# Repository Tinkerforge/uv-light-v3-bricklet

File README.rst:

UV Light Bricklet 3.0
=====================

This repository contains the firmware source code and the hardware design
files. The documentation generator configs can be found at
https://github.com/Tinkerforge/generators

Repository Content
------------------

software/:
 * examples/: Examples for all supported languages
 * build/: Compiled files
 * src/: Source code of firmware
 * Makefile: Makefile to build project

hardware/:
 * Contains KiCad project files and additionally schematics as PDF

datasheets/:
 * Contains datasheets for sensors and complex ICs that are used

Hardware
--------

The hardware is designed with the open source EDA Suite KiCad
(http://www.kicad.org). Before you are able to open the files,
you have to install the Tinkerforge kicad-libraries
(https://github.com/Tinkerforge/kicad-libraries). You can either clone
them directly in hardware/ or clone them in a separate folder and
symlink them into hardware/
(ln -s kicad_path/kicad-libraries project_path/hardware). After that you
can open the .pro file in hardware/ with KiCad and from there view and
modify the schematics and the PCB layout.

Software
--------

If you want to do your own Brick/Bricklet firmware development we highly
recommend that you use our build environment setup script and read the
tutorial (https://www.tinkerforge.com/en/doc/Tutorials/Tutorial_Build_Environment/Tutorial.html).

To compile the C code we recommend you to install the newest GNU Arm Embedded
Toolchain (https://launchpad.net/gcc-arm-embedded/+download).
You also need to install bricklib2 (https://github.com/Tinkerforge/bricklib2).

You can either clone it directly in software/src/ or clone it in a
separate folder and symlink it into software/src/
(ln -s bricklib_path/bricklib2 project_path/software/src/). Finally make sure to
have CMake installed (http://www.cmake.org/cmake/resources/software.html).

After that you can build the firmware by invoking make in software/.
The firmware (.zbin) can then be found in software/build/ and uploaded
with brickv (click button "Flashing" on start screen).

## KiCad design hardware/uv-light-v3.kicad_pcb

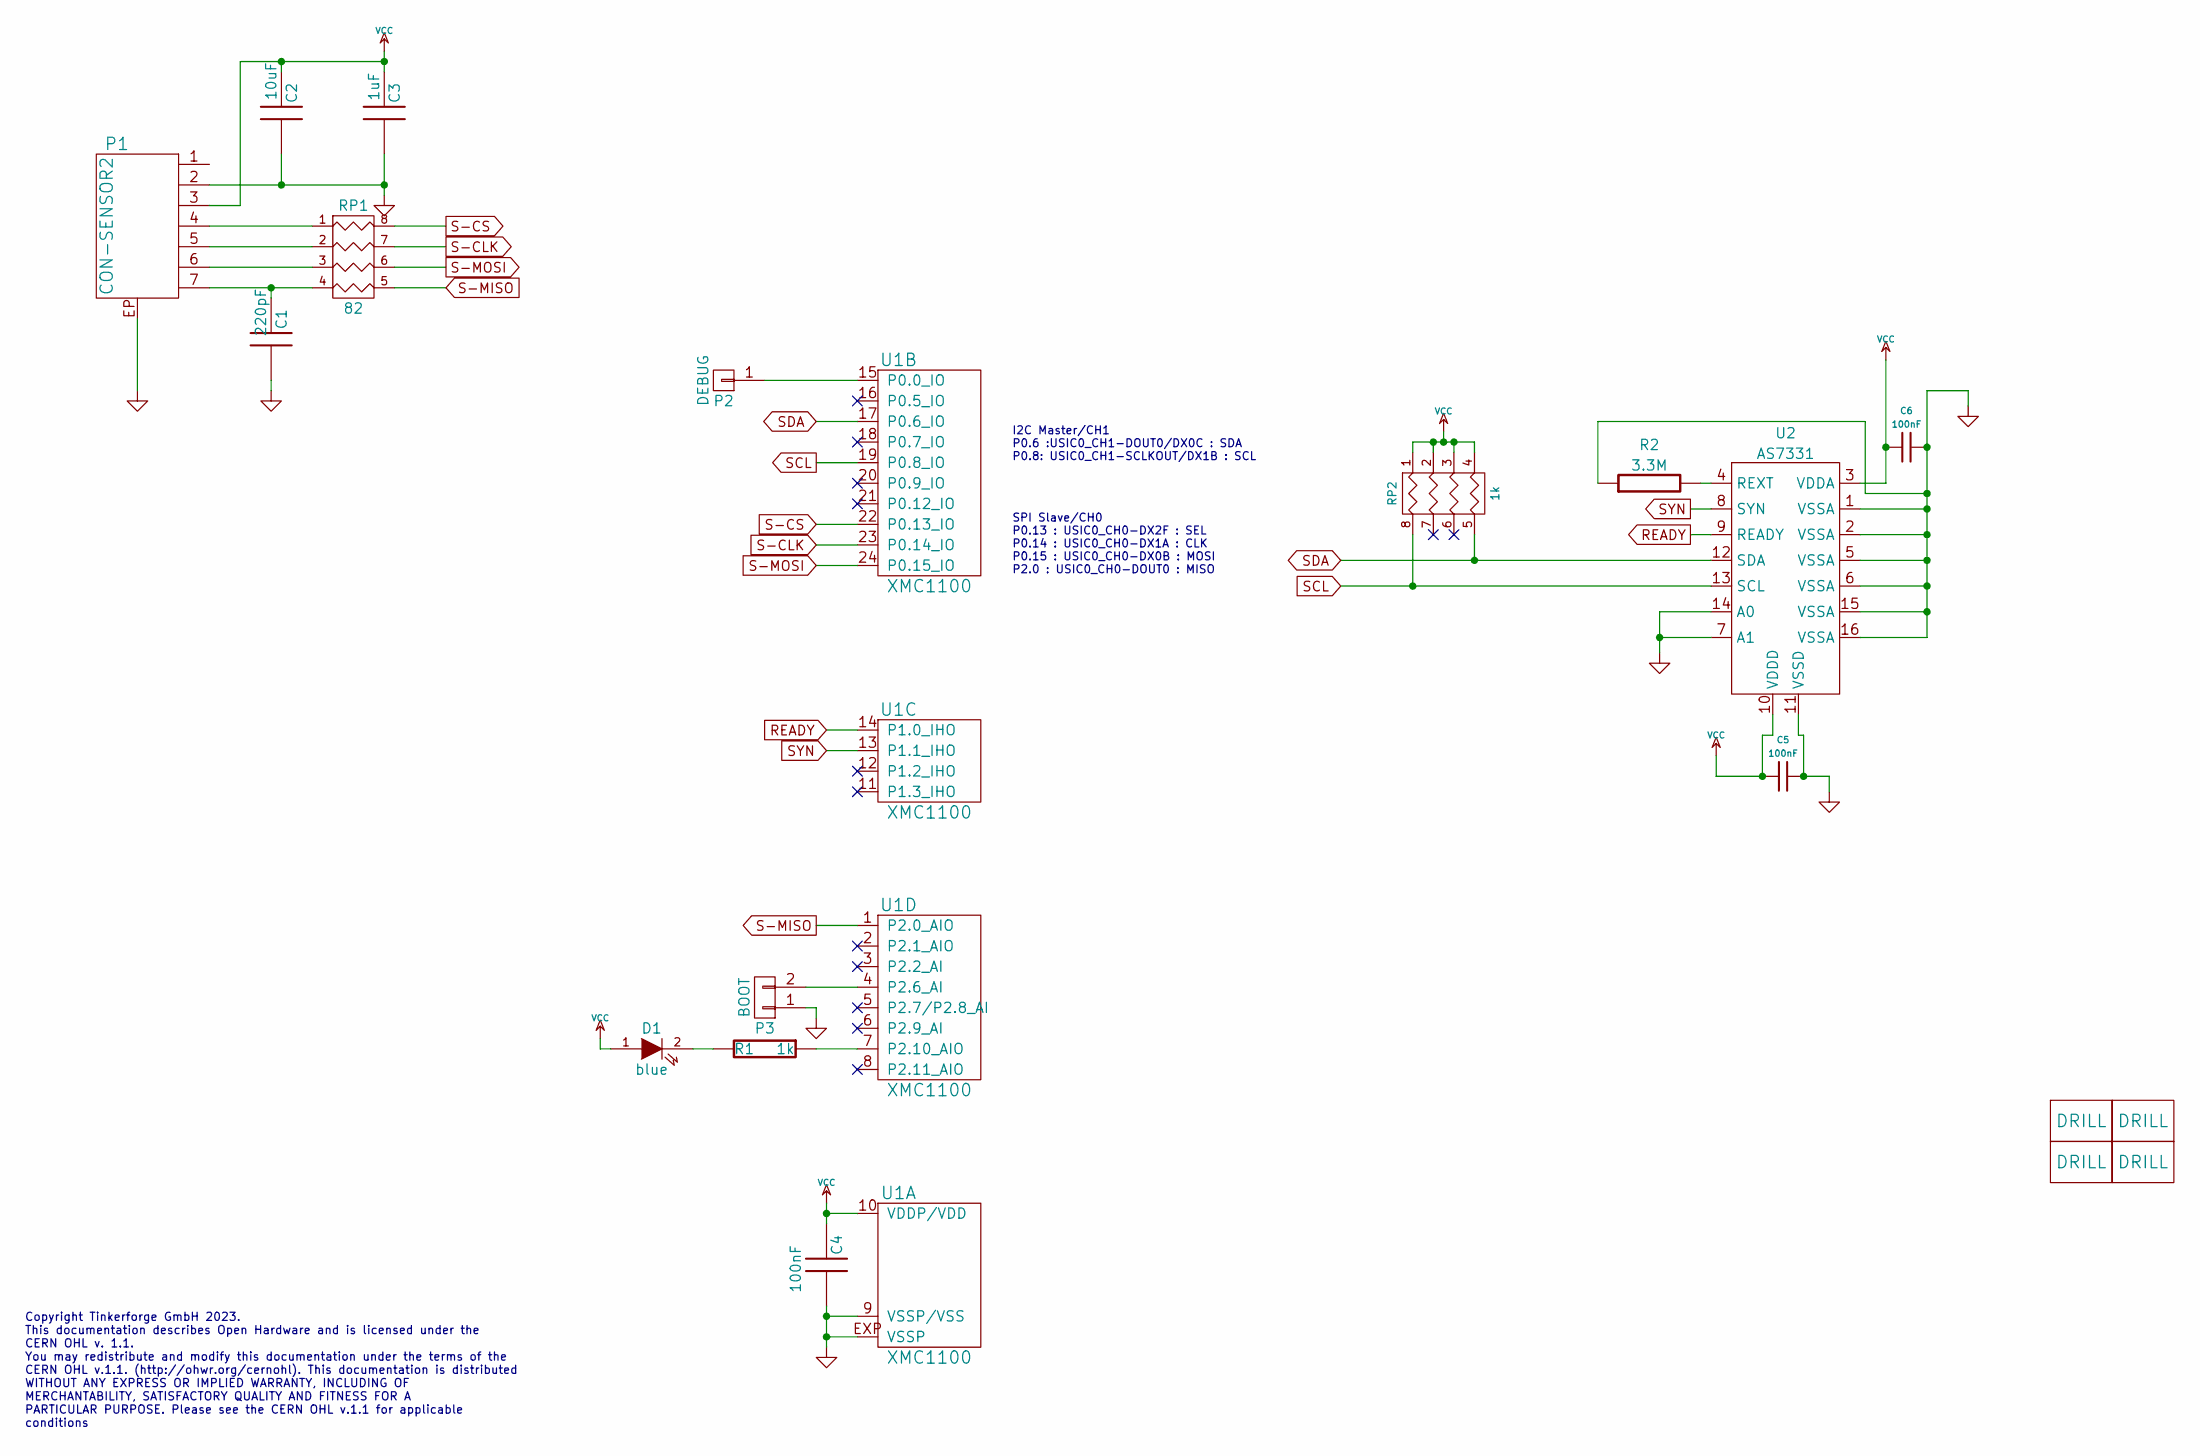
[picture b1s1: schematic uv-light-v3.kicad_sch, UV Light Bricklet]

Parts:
C1: 220pF; C0402F
C2: 10uF; C0805
C3: 1uF; C0603F
C4, C5, C6: 100nF; C0603F
D1: blue; D0603F
P1: CON-SENSOR2
P2: DEBUG; DEBUG_PAD
P3: BOOT; SolderJumper
R1: 1k; R0603F
R2: 3.3M; R0603F
RP1: 82; 4X0402
RP2: 1k; 0603X4
U1: XMC1100; QFN24-4x4mm-0.5mm
U2: AS7331
U3, U4, U5, U6: DRILL; DRILL_NP

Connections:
GND: C1.1, C2.1, C3.1, C4.1, C5.2, C6.2, P1.2, P1.EP, P3.1, R2.1, U1.9 (VSSP/VSS), U1.EXP (VSSP), U2.1 (VSSA), U2.2 (VSSA), U2.5 (VSSA), U2.6 (VSSA), U2.7 (A1), U2.11 (VSSD), U2.14 (A0), U2.15 (VSSA), U2.16 (VSSA)
unnamed: C1.2, P1.7, RP1.4
unnamed: D1.2 (K), R1.2
unnamed: P1.4, RP1.1
unnamed: P1.5, RP1.2
unnamed: P1.6, RP1.3
unnamed: P2.1, U1.15 (P0.0_IO)
unnamed: P3.2, U1.4 (P2.6_AI)
unnamed: R1.1, U1.7 (P2.10_AIO)
unnamed: R2.2, U2.4 (REXT)
READY: U1.14 (P1.0_IHO), U2.9 (READY)
S-CLK: RP1.7 (R2), U1.23 (P0.14_IO)
S-CS: RP1.8 (R1), U1.22 (P0.13_IO)
S-MISO: RP1.5 (R4), U1.1 (P2.0_AIO)
S-MOSI: RP1.6 (R3), U1.24 (P0.15_IO)
SCL: RP2.8 (R1), U1.19 (P0.8_IO), U2.13 (SCL)
SDA: RP2.5 (R4), U1.17 (P0.6_IO), U2.12 (SDA)
SYN: U1.13 (P1.1_IHO), U2.8 (SYN)
VCC: C2.2, C3.2, C4.2, C5.1, C6.1, D1.1 (A), P1.3, RP2.1, RP2.2, RP2.3, RP2.4, U1.10 (VDDP/VDD), U2.3 (VDDA), U2.10 (VDDD)

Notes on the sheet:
I2C Master/CH1 P0.6 :USIC0_CH1-DOUT0/DX0C : SDA P0.8: USIC0_CH1-SCLKOUT/DX1B : SCL
SPI Slave/CH0 P0.13 : USIC0_CH0-DX2F : SEL P0.14 : USIC0_CH0-DX1A : CLK P0.15 : USIC0_CH0-DX0B : MOSI P2.0 : USIC0_CH0-DOUT0 : MISO
Copyright Tinkerforge GmbH 2023. This documentation describes Open Hardware and is licensed under the CERN OHL v. 1.1. You may redistribute and modify this documentation under the terms of the CERN OHL v.1.1. (http://ohwr.org/cernohl). This documentation is distributed WITHOUT ANY EXPRESS OR IMPLIE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

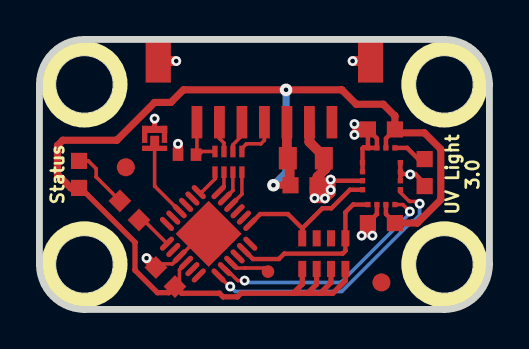
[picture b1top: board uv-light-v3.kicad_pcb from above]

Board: 2 copper layers, 25.0 x 15.0 mm, 24 parts (2 on the bottom side), 19 nets.

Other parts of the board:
Fiducial_Mark: VAL**; Fiducial_Mark
Fiducial_Mark#2: VAL**; Fiducial_Mark
VAL: WEEE_7mm
VAL#2: CE_5mm

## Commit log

2023-05-09 initial push
2023-05-09 schematic done
2023-05-10 first pcb layout
2023-05-10 ready for prototype
2023-07-26 changed mask layer to 0mm cutout, removed traces under AS7331

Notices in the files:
hardware/uv-light-v3.kicad_pcb:
Licensed under CERN OHL v.1.1
Copyright (©) 2023, T.Schneidermann
